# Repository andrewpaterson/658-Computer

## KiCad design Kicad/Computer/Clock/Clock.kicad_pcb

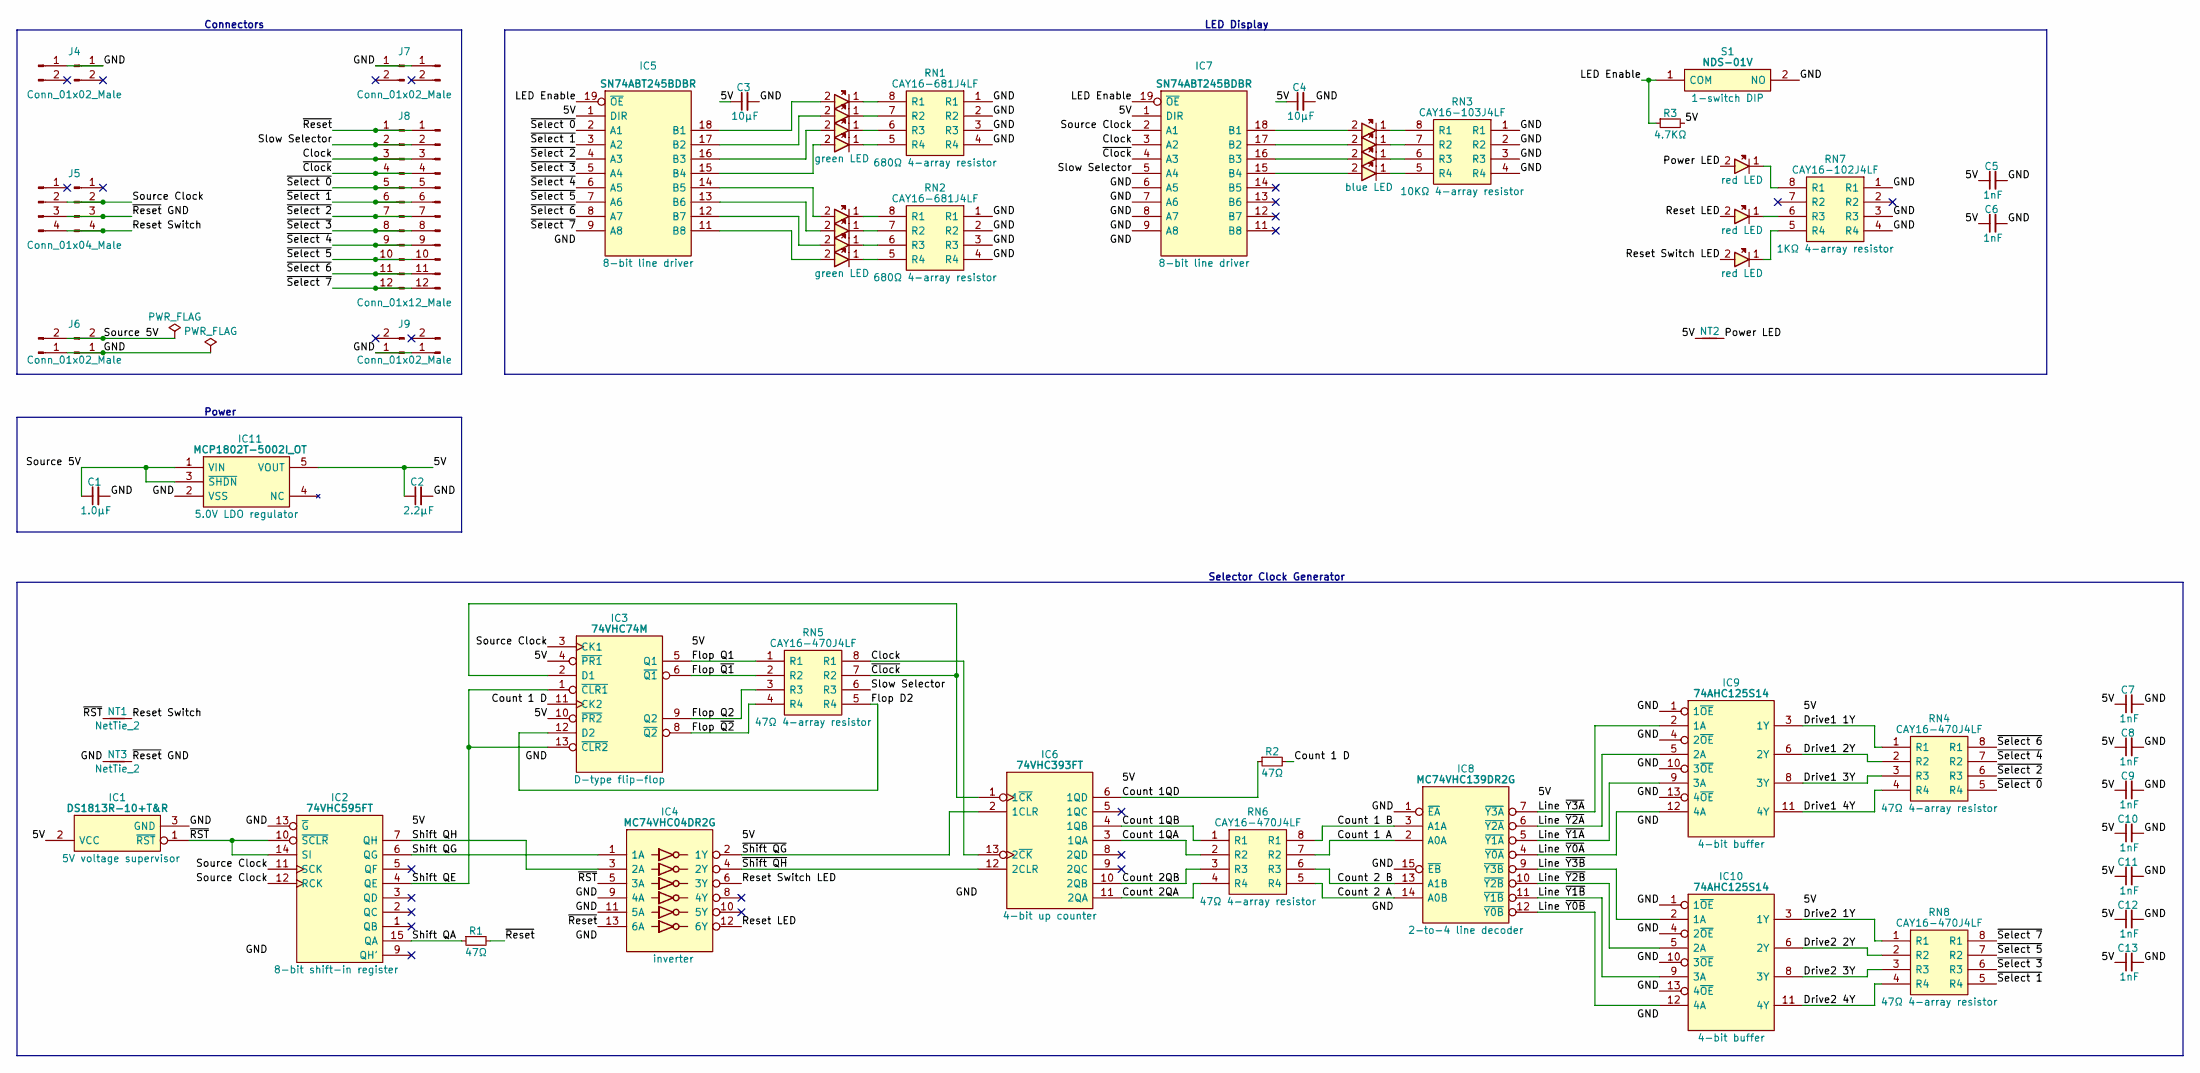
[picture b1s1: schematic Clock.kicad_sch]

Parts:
C1, C2, C3, C4, C5, C6, C7, C8, C9, C10, C11, C12, C13: C_0805
IC1: DS1813R-10+T&R; SOT95P237X112-3N; Mouser Part Number 700-DS1813R-10T&R
IC2: 74VHC595FT; SOP65P640X120-16N; Manufacturer_Part_Number 74VHC595FT; Mouser Part Number 757-74VHC595FT
IC3: 74VHC74M; SOIC127P600X175-14N; Manufacturer_Part_Number 74VHC74M; Mouser Part Number 512-74VHC74M
IC4: MC74VHC04DR2G; SOIC127P600X175-14N; Manufacturer_Part_Number MC74VHC04DR2G; Mouser Part Number 863-MC74VHC04DR2G
IC5, IC7: SN74ABT245BDBR; SOP65P780X200-20N; Manufacturer_Part_Number SN74ABT245BDBR; Mouser Part Number 595-SN74ABT245BDBR
IC6: 74VHC393FT; SOP65P640X120-14N; Manufacturer_Part_Number 74VHC393FT; Mouser Part Number 757-74VHC393FT
IC8: MC74VHC139DR2G; SOIC127P602X173-16N; Manufacturer_Part_Number MC74VHC139DTR2G; Mouser Part Number 863-MC74VHC139DTR2G
IC9, IC10: 74AHC125S14; SOIC127P600X173-14N; Manufacturer_Part_Number 74AHC125S14-13; Mouser Part Number 621-74AHC125S14-13
IC11: MCP1802T-5002I_OT; SOT95P270X145-5N; Manufacturer_Part_Number MCP1802T-5002I/OT; Mouser Part Number 579-MCP1802T-5002IOT
J1, J3, J4, J6, J7, J9, J10, J12: Conn_01x02_Male
J2, J5: Conn_01x04_Male
J8, J11: Conn_01x12_Male
LD10, LD11, LD12: 150224BS73100A; Manufacturer_Part_Number 150224BS73100A; Mouser Part Number 710-150224BS73100A
LD13, LD14, LD15: 150224SS73100; 150224SS73100A; Manufacturer_Part_Number 150224SS73100; Mouser Part Number 710-150224SS73100
LED1, LED2, LED3, LED4, LED5, LED6, LED7, LED8: 150224VS73100A; Manufacturer_Part_Number 150224VS73100A; Mouser Part Number 710-150224VS73100A
LED9: 150224BS73100A; Manufacturer_Part_Number 150224BS73100A; Mouser Part Number 710-150224BS73100A
NT1, NT3: NetTie_2
NT2: NetTie; NetTie-2_SMD_Pad0.5mm
R1, R2, R3: R_0805
RN1, RN2: CAY16-681J4LF; CAY16-J4; Manufacturer_Part_Number CAY16-681J4LF; Mouser Part Number 652-CAY16-681J4LF
RN3: CAY16-103J4LF; CAY16-J4; Manufacturer_Part_Number CAY16-103J4LF; Mouser Part Number 652-CAY16-103J4LF
RN4, RN5, RN6, RN8: CAY16-470J4LF; CAY16470J4LF; Manufacturer_Part_Number CAY16-470J4LF; Mouser Part Number 652-CAY16-470J4LF
RN7: CAY16-102J4LF; CAY16-J4; Manufacturer_Part_Number CAY16-102J4LF; Mouser Part Number 652-CAY16-102J4LF
S1: NDS-01V; NDS01V; Mouser Part Number 113-NDS01V

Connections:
5V: C2.1, C3.1, C4.1, C5.1, C6.1, C7.1, C8.1, C9.1, C10.1, C11.1, C12.1, C13.1, IC1.2 (VCC), IC2.16 (5V), IC3.4 (~PR1), IC3.10 (~PR2), IC3.14 (5V), IC4.14 (5V), IC5.1 (DIR), IC5.20 (5V), IC6.14 (5V), IC7.1 (DIR), IC7.20 (5V), IC8.16 (5V), IC9.14 (VCC), IC10.14 (VCC), IC11.5 (VOUT), NT2.1, R3.2
/Clock: IC6.13 (2~CK), IC7.3 (A2), J8.3, J11.3, RN5.8 (R1)
/Count 1 A: IC8.2 (A0A), RN6.7 (R2)
/Count 1 B: IC8.3 (A1A), RN6.8 (R1)
/Count 1 D: IC3.11 (CK2), R2.2
/Count 1QA: IC6.3 (1QA), RN6.2 (R2)
/Count 1QB: IC6.4 (1QB), RN6.1 (R1)
/Count 1QD: IC6.6 (1QD), R2.1
/Count 2 A: IC8.14 (A0B), RN6.5 (R4)
/Count 2 B: IC8.13 (A1B), RN6.6 (R3)
/Count 2QA: IC6.11 (2QA), RN6.4 (R4)
/Count 2QB: IC6.10 (2QB), RN6.3 (R3)
/Drive1 1Y: IC9.3 (1Y), RN4.1 (R1)
/Drive1 2Y: IC9.6 (2Y), RN4.2 (R2)
/Drive1 3Y: IC9.8 (3Y), RN4.3 (R3)
/Drive1 4Y: IC9.11 (4Y), RN4.4 (R4)
/Drive2 1Y: IC10.3 (1Y), RN8.1 (R1)
/Drive2 2Y: IC10.6 (2Y), RN8.2 (R2)
/Drive2 3Y: IC10.8 (3Y), RN8.3 (R3)
/Drive2 4Y: IC10.11 (4Y), RN8.4 (R4)
/Flop D2: IC3.12 (D2), RN5.5 (R4)
/Flop Q1: IC3.5 (Q1), RN5.1 (R1)
/Flop Q2: IC3.9 (Q2), RN5.3 (R3)
/Flop ~Q1: IC3.6 (~Q1), RN5.2 (R2)
/Flop ~Q2: IC3.8 (~Q2), RN5.4 (R4)
/LED Enable: IC5.19 (~OE), IC7.19 (~OE), R3.1, S1.1 (COM)
/Line ~Y0A: IC8.4 (~Y0A), IC9.12 (4A)
/Line ~Y0B: IC8.12 (~Y0B), IC10.12 (4A)
/Line ~Y1A: IC8.5 (~Y1A), IC9.9 (3A)
/Line ~Y1B: IC8.11 (~Y1B), IC10.9 (3A)
/Line ~Y2A: IC8.6 (~Y2A), IC9.5 (2A)
/Line ~Y2B: IC8.10 (~Y2B), IC10.5 (2A)
/Line ~Y3A: IC8.7 (~Y3A), IC9.2 (1A)
/Line ~Y3B: IC8.9 (~Y3B), IC10.2 (1A)
/Power LED: LD13.2, NT2.2
/Reset LED: IC4.12 (6Y), LD14.2
/Reset Switch: J2.4, J5.4, NT1.1
/Reset Switch LED: IC4.6 (3Y), LD15.2
/Shift QA: IC2.15 (QA), R1.1
/Shift QE: IC2.4 (QE), IC3.1 (~CLR1), IC3.13 (~CLR2)
/Shift QG: IC2.6 (QG), IC4.1 (1A)
/Shift QH: IC2.7 (QH), IC4.3 (2A)
/Slow Selector: IC7.5 (A4), J8.2, J11.2, RN5.6 (R3)
/Source 5V: C1.1, IC11.1 (VIN), IC11.3 (~SHDN), J3.2, J6.2
/Source Clock: IC2.11 (SCK), IC2.12 (RCK), IC3.3 (CK1), IC7.2 (A1), J2.2, J5.2
/~Clock: IC3.2 (D1), IC6.1 (1~CK), IC7.4 (A3), J8.4, J11.4, RN5.7 (R2)
/~RST: IC1.1 (~RST), IC2.10 (~SCLR), IC2.14 (SI), IC4.5 (3A), NT1.2
/~Reset: IC4.13 (6A), J8.1, J11.1, R1.2
/~Reset GND: J2.3, J5.3, NT3.1
/~Select 0: IC5.2 (A1), J8.5, J11.5, RN4.5 (R4)
/~Select 1: IC5.3 (A2), J8.6, J11.6, RN8.5 (R4)
/~Select 2: IC5.4 (A3), J8.7, J11.7, RN4.6 (R3)
/~Select 3: IC5.5 (A4), J8.8, J11.8, RN8.6 (R3)
/~Select 4: IC5.6 (A5), J8.9, J11.9, RN4.7 (R2)
/~Select 5: IC5.7 (A6), J8.10, J11.10, RN8.7 (R2)
/~Select 6: IC5.8 (A7), J8.11, J11.11, RN4.8 (R1)
/~Select 7: IC5.9 (A8), J8.12, J11.12, RN8.8 (R1)
/~Shift QG: IC4.2 (1Y), IC6.2 (1CLR)
/~Shift QH: IC4.4 (2Y), IC6.12 (2CLR)
GND: C1.2, C2.2, C3.2, C4.2, C5.2, C6.2, C7.2, C8.2, C9.2, C10.2, C11.2, C12.2, C13.2, IC1.3 (GND), IC2.8 (GND), IC2.13 (~G), IC3.7 (GND), IC4.7 (GND), IC4.9 (4A), IC4.11 (5A), IC5.10 (GND), IC6.7 (GND), IC7.6 (A5), IC7.7 (A6), IC7.8 (A7), IC7.9 (A8), IC7.10 (GND), IC8.1 (~EA), IC8.8 (GND), IC8.15 (~EB), IC9.1 (1~OE), IC9.4 (2~OE), IC9.7 (GND), IC9.10 (3~OE), IC9.13 (4~OE), IC10.1 (1~OE), IC10.4 (2~OE), IC10.7 (GND), IC10.10 (3~OE), IC10.13 (4~OE), IC11.2 (VSS), J1.1, J3.1, J4.1, J6.1, J7.1, J9.1, J10.1, J12.1, NT3.2, RN1.1 (R1), RN1.2 (R2), RN1.3 (R3), RN1.4 (R4), RN2.1 (R1), RN2.2 (R2), RN2.3 (R3), RN2.4 (R4), RN3.1 (R1), RN3.2 (R2), RN3.3 (R3), RN3.4 (R4), RN7.1 (R1), RN7.3 (R3), RN7.4 (R4), S1.2 (NO)
unnamed: IC5.11 (B8), LED8.2
unnamed: IC5.12 (B7), LED7.2
unnamed: IC5.13 (B6), LED6.2
unnamed: IC5.14 (B5), LED5.2
unnamed: IC5.15 (B4), LED4.2
unnamed: IC5.16 (B3), LED3.2
unnamed: IC5.17 (B2), LED2.2
unnamed: IC5.18 (B1), LED1.2
unnamed: IC7.15 (B4), LD12.2
unnamed: IC7.16 (B3), LD11.2
unnamed: IC7.17 (B2), LD10.2
unnamed: IC7.18 (B1), LED9.2
unnamed: LD10.1, RN3.7 (R2)
unnamed: LD11.1, RN3.6 (R3)
unnamed: LD12.1, RN3.5 (R4)
unnamed: LD13.1, RN7.8 (R1)
unnamed: LD14.1, RN7.6 (R3)
unnamed: LD15.1, RN7.5 (R4)
unnamed: LED1.1, RN1.8 (R1)
unnamed: LED2.1, RN1.7 (R2)
unnamed: LED3.1, RN1.6 (R3)
unnamed: LED4.1, RN1.5 (R4)
unnamed: LED5.1, RN2.8 (R1)
unnamed: LED6.1, RN2.7 (R2)
unnamed: LED7.1, RN2.6 (R3)
unnamed: LED8.1, RN2.5 (R4)
unnamed: LED9.1, RN3.8 (R1)

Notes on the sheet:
LED Display
Connectors
Power
Selector Clock Generator

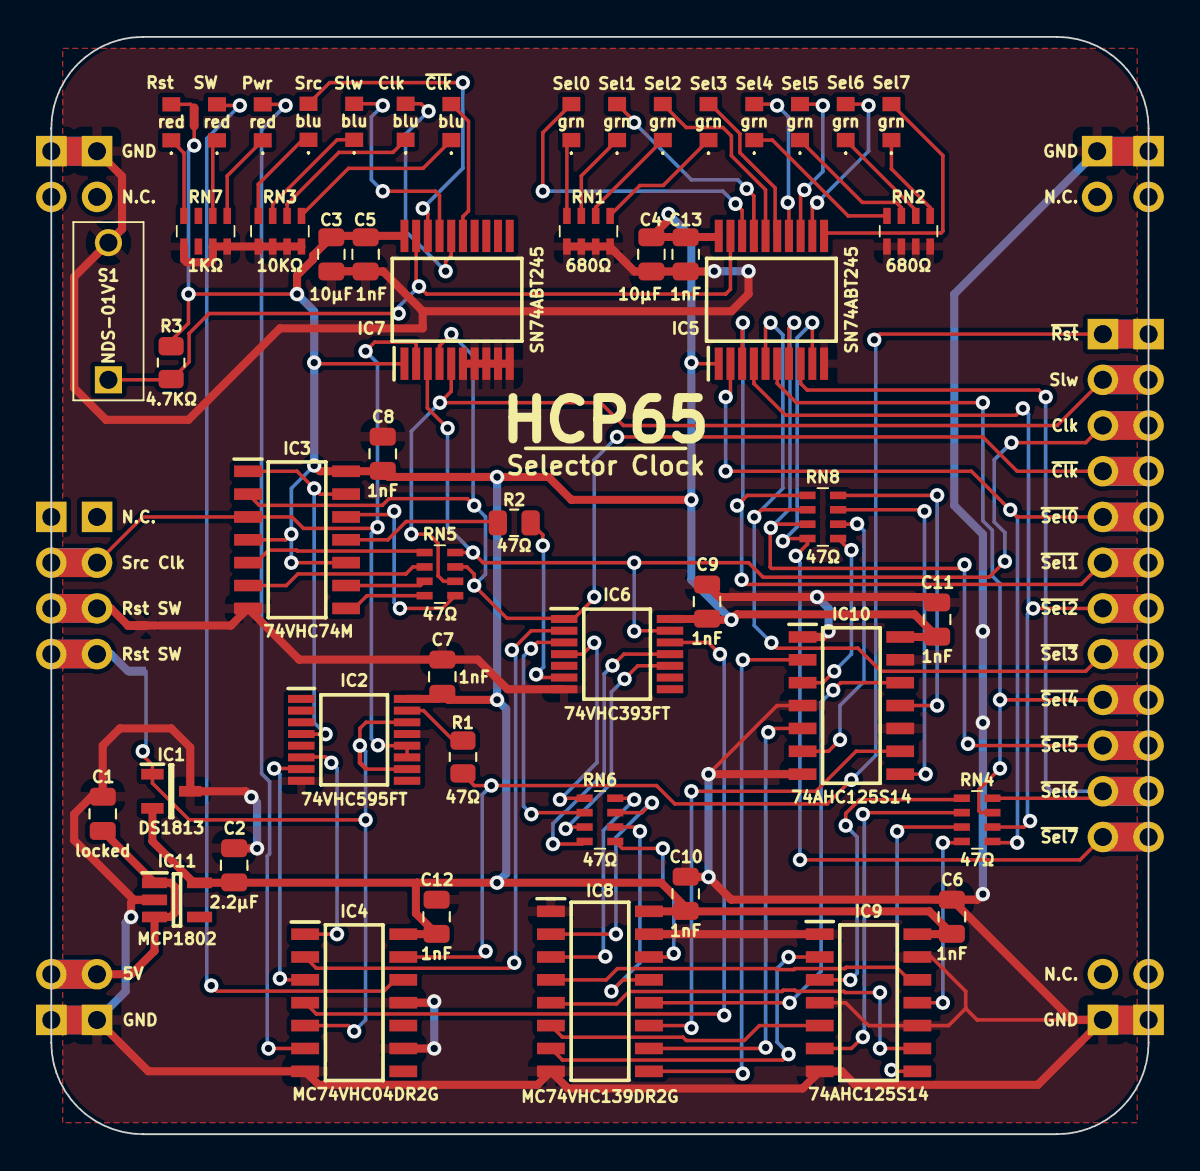
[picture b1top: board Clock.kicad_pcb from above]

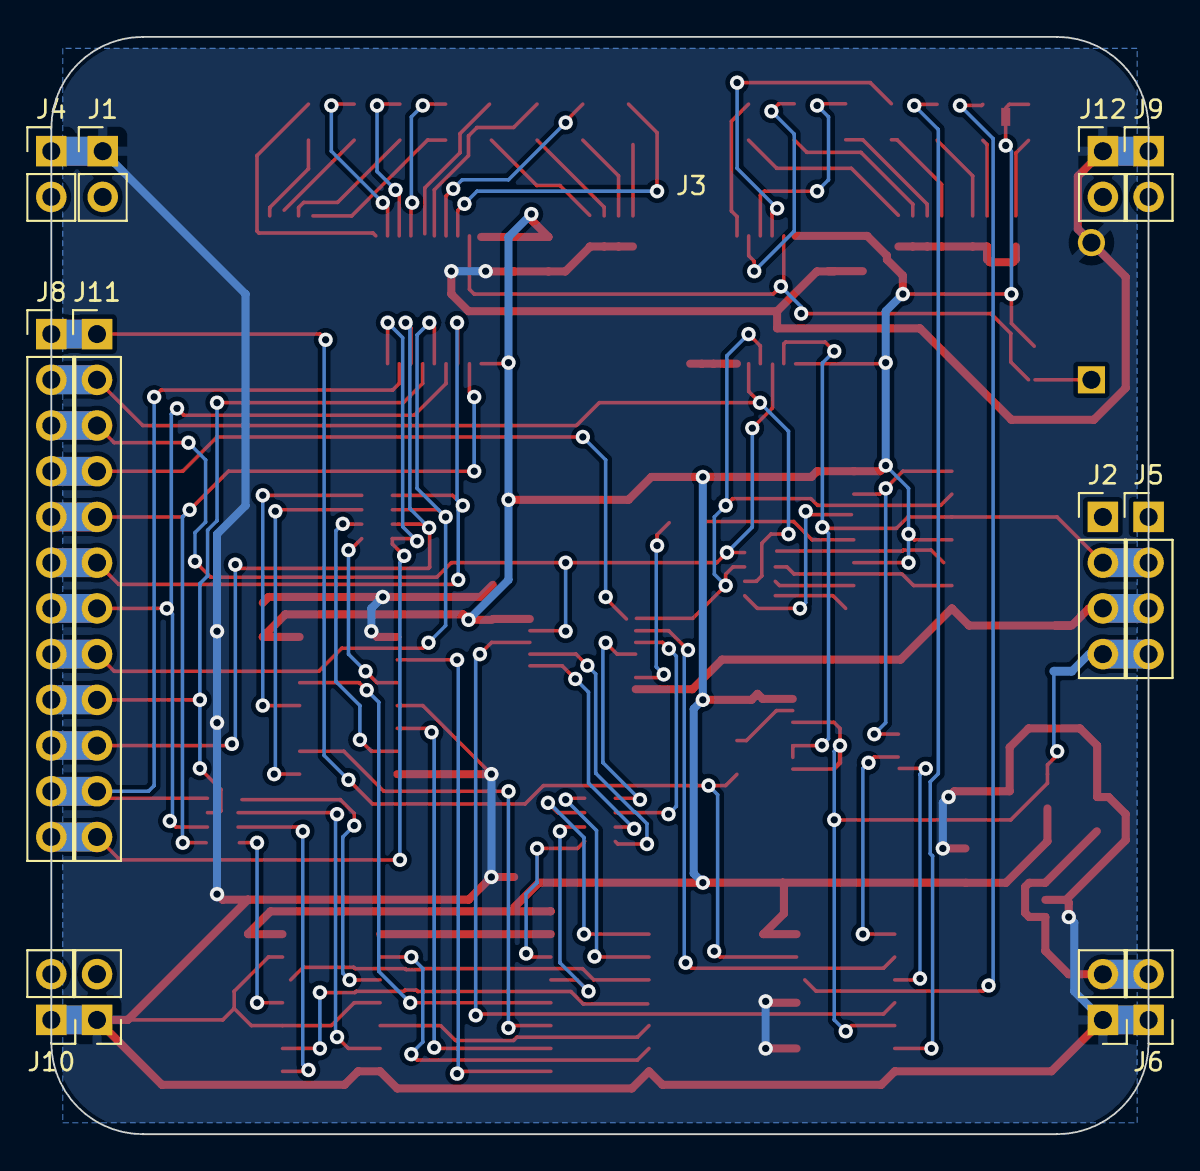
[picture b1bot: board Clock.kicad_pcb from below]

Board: 2 copper layers, 61.0 x 61.0 mm, 66 parts (13 on the bottom side), 87 nets.

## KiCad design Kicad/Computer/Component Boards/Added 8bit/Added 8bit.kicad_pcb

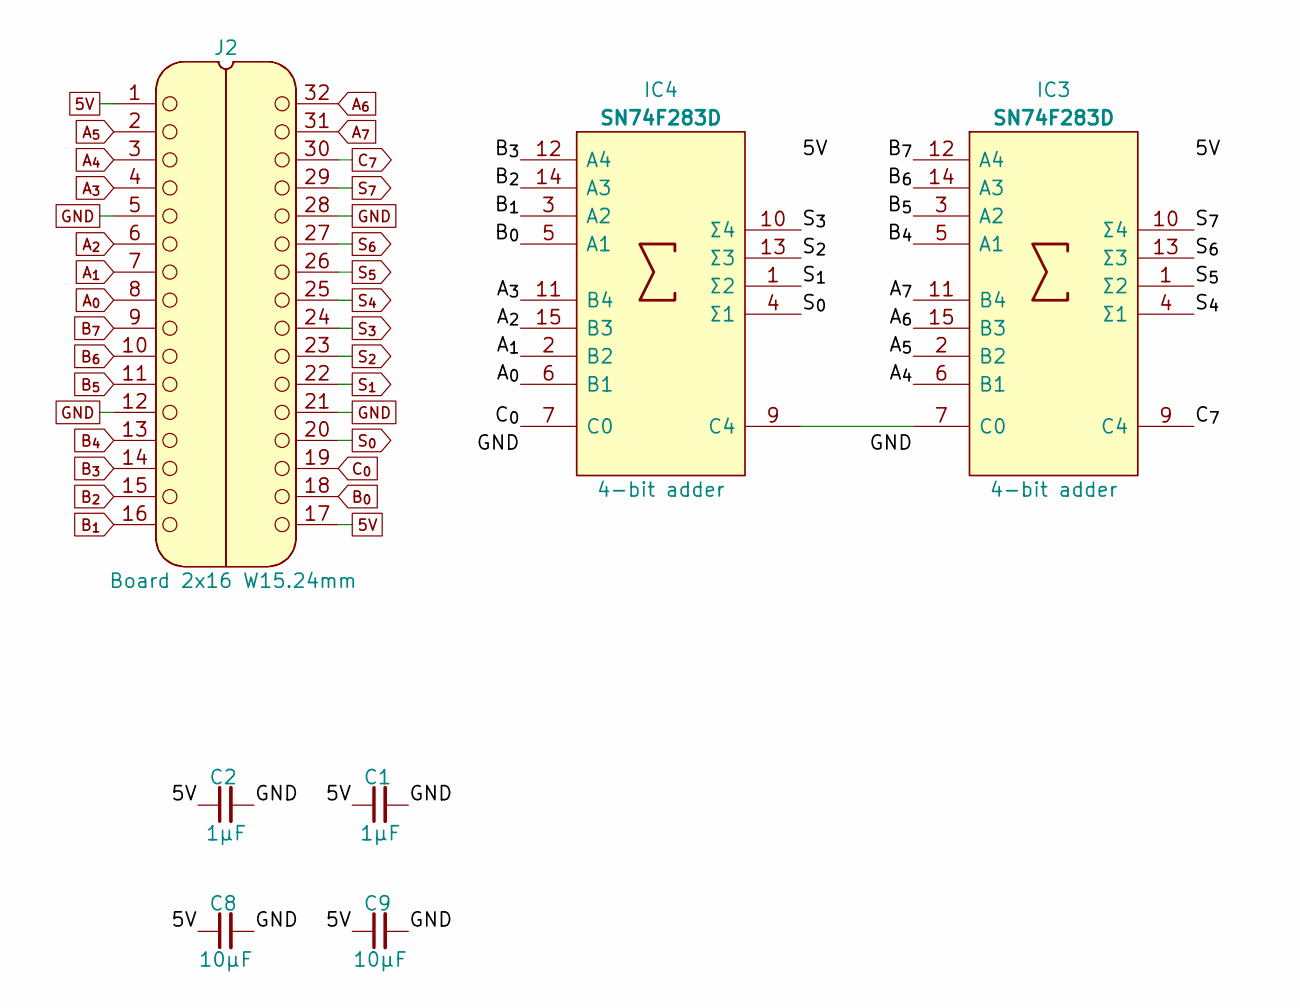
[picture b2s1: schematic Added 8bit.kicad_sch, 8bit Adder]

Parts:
C1, C2: 1μF; C_0805
C8, C9: 10µF; C_0805
IC3, IC4: SN74F283D; SOIC127P600X175-16N; Mouser Part Number 595-SN74F283D
J2: Board 2x16 W15.24mm; DIP-32_Board_W15.24mm

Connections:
5V: C1.1, C2.1, C8.1, C9.1, IC3.16 (5V), IC4.16 (5V), J2.1, J2.17
A_{0}: IC4.6 (B1), J2.8
A_{1}: IC4.2 (B2), J2.7
A_{2}: IC4.15 (B3), J2.6
A_{3}: IC4.11 (B4), J2.4
A_{4}: IC3.6 (B1), J2.3
A_{5}: IC3.2 (B2), J2.2
A_{6}: IC3.15 (B3), J2.32
A_{7}: IC3.11 (B4), J2.31
B_{0}: IC4.5 (A1), J2.18
B_{1}: IC4.3 (A2), J2.16
B_{2}: IC4.14 (A3), J2.15
B_{3}: IC4.12 (A4), J2.14
B_{4}: IC3.5 (A1), J2.13
B_{5}: IC3.3 (A2), J2.11
B_{6}: IC3.14 (A3), J2.10
B_{7}: IC3.12 (A4), J2.9
C_{0}: IC4.7 (C0), J2.19
C_{7}: IC3.9 (C4), J2.30
GND: C1.2, C2.2, C8.2, C9.2, IC3.8 (GND), IC4.8 (GND), J2.5, J2.12, J2.21, J2.28
unnamed: IC3.7 (C0), IC4.9 (C4)
S_{0}: IC4.4 (Σ1), J2.20
S_{1}: IC4.1 (Σ2), J2.22
S_{2}: IC4.13 (Σ3), J2.23
S_{3}: IC4.10 (Σ4), J2.24
S_{4}: IC3.4 (Σ1), J2.25
S_{5}: IC3.1 (Σ2), J2.26
S_{6}: IC3.13 (Σ3), J2.27
S_{7}: IC3.10 (Σ4), J2.29

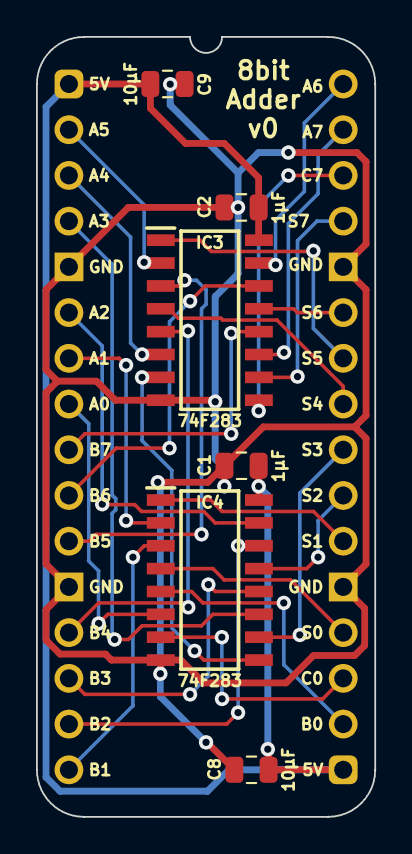
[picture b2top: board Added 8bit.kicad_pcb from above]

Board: 2 copper layers, 18.8 x 43.3 mm, 7 parts (0 on the bottom side), 29 nets.

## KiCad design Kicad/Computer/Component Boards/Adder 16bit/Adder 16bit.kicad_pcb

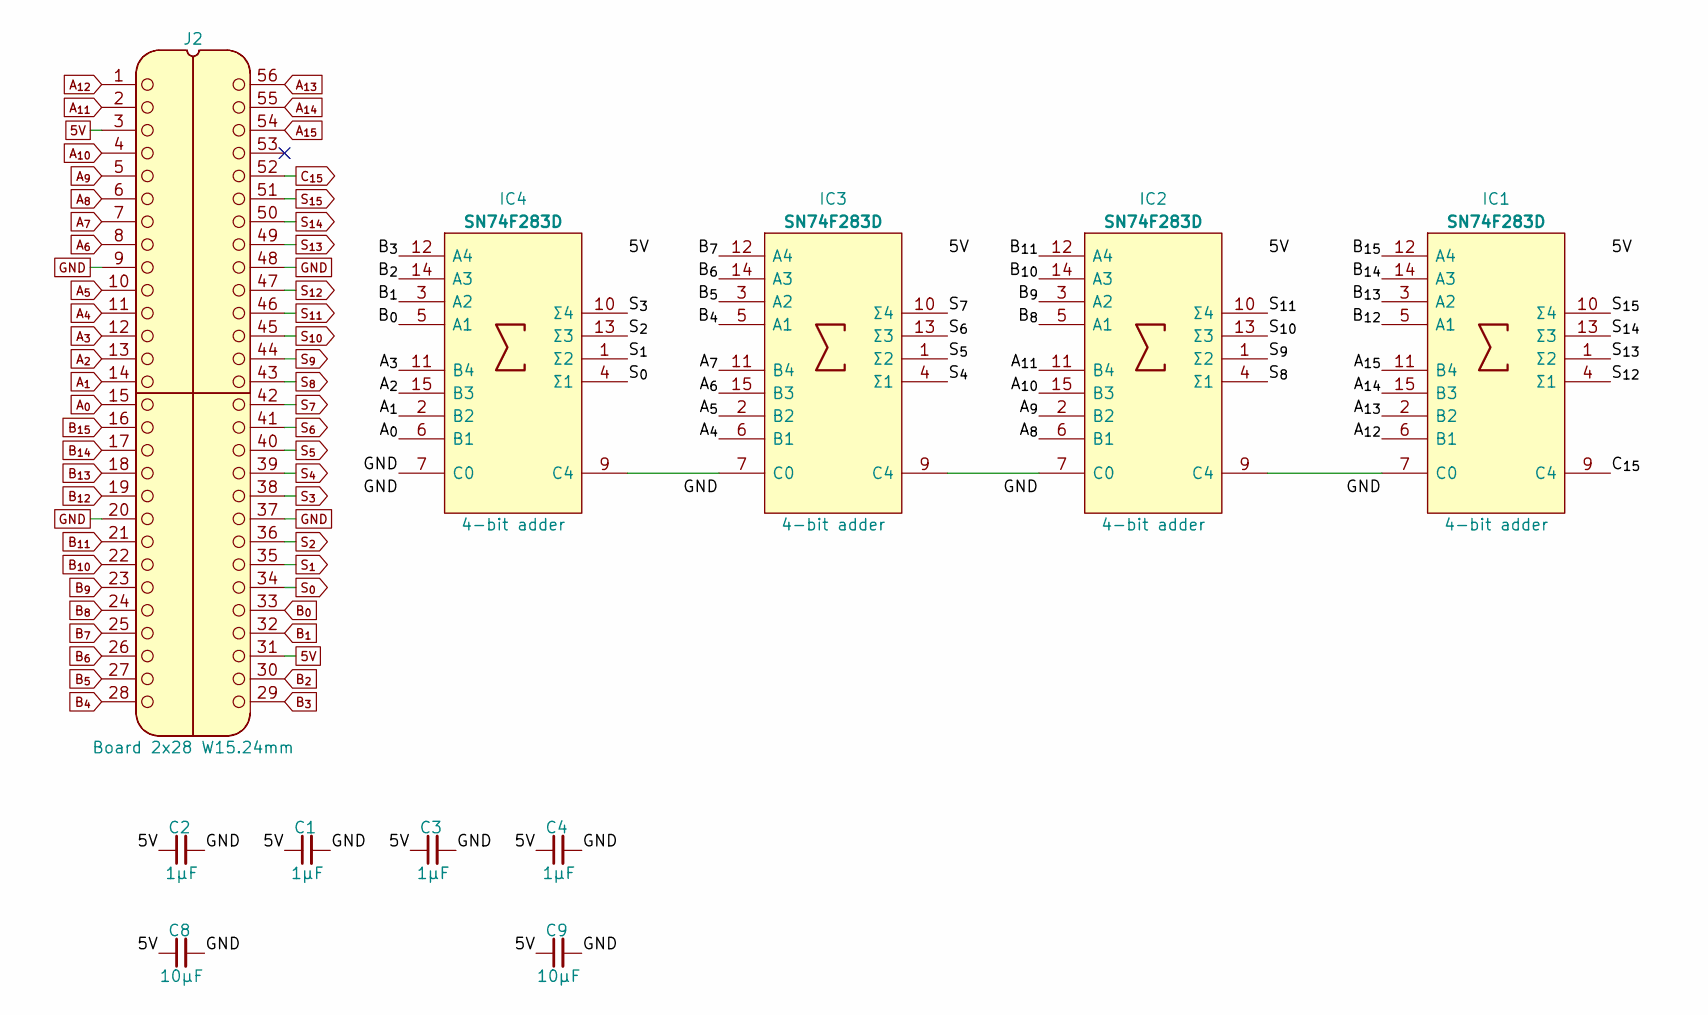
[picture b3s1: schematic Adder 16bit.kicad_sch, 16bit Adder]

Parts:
C1, C2, C3, C4: 1μF; C_0805
C8, C9: 10µF; C_0805
IC1, IC2, IC3, IC4: SN74F283D; SOIC127P600X175-16N; Mouser Part Number 595-SN74F283D
J2: Board 2x28 W15.24mm; DIP-56_Board_W15.24mm

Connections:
5V: C1.1, C2.1, C3.1, C4.1, C8.1, C9.1, IC1.16 (5V), IC2.16 (5V), IC3.16 (5V), IC4.16 (5V), J2.3, J2.31
A_{0}: IC4.6 (B1), J2.15
A_{1}: IC4.2 (B2), J2.14
A_{2}: IC4.15 (B3), J2.13
A_{3}: IC4.11 (B4), J2.12
A_{4}: IC3.6 (B1), J2.11
A_{5}: IC3.2 (B2), J2.10
A_{6}: IC3.15 (B3), J2.8
A_{7}: IC3.11 (B4), J2.7
A_{8}: IC2.6 (B1), J2.6
A_{9}: IC2.2 (B2), J2.5
A_{10}: IC2.15 (B3), J2.4
A_{11}: IC2.11 (B4), J2.2
A_{12}: IC1.6 (B1), J2.1
A_{13}: IC1.2 (B2), J2.56
A_{14}: IC1.15 (B3), J2.55
A_{15}: IC1.11 (B4), J2.54
B_{0}: IC4.5 (A1), J2.33
B_{1}: IC4.3 (A2), J2.32
B_{2}: IC4.14 (A3), J2.30
B_{3}: IC4.12 (A4), J2.29
B_{4}: IC3.5 (A1), J2.28
B_{5}: IC3.3 (A2), J2.27
B_{6}: IC3.14 (A3), J2.26
B_{7}: IC3.12 (A4), J2.25
B_{8}: IC2.5 (A1), J2.24
B_{9}: IC2.3 (A2), J2.23
B_{10}: IC2.14 (A3), J2.22
B_{11}: IC2.12 (A4), J2.21
B_{12}: IC1.5 (A1), J2.19
B_{13}: IC1.3 (A2), J2.18
B_{14}: IC1.14 (A3), J2.17
B_{15}: IC1.12 (A4), J2.16
C_{15}: IC1.9 (C4), J2.52
GND: C1.2, C2.2, C3.2, C4.2, C8.2, C9.2, IC1.8 (GND), IC2.8 (GND), IC3.8 (GND), IC4.7 (C0), IC4.8 (GND), J2.9, J2.20, J2.37, J2.48
unnamed: IC1.7 (C0), IC2.9 (C4)
unnamed: IC2.7 (C0), IC3.9 (C4)
unnamed: IC3.7 (C0), IC4.9 (C4)
S_{0}: IC4.4 (Σ1), J2.34
S_{1}: IC4.1 (Σ2), J2.35
S_{2}: IC4.13 (Σ3), J2.36
S_{3}: IC4.10 (Σ4), J2.38
S_{4}: IC3.4 (Σ1), J2.39
S_{5}: IC3.1 (Σ2), J2.40
S_{6}: IC3.13 (Σ3), J2.41
S_{7}: IC3.10 (Σ4), J2.42
S_{8}: IC2.4 (Σ1), J2.43
S_{9}: IC2.1 (Σ2), J2.44
S_{10}: IC2.13 (Σ3), J2.45
S_{11}: IC2.10 (Σ4), J2.46
S_{12}: IC1.4 (Σ1), J2.47
S_{13}: IC1.1 (Σ2), J2.49
S_{14}: IC1.13 (Σ3), J2.50
S_{15}: IC1.10 (Σ4), J2.51

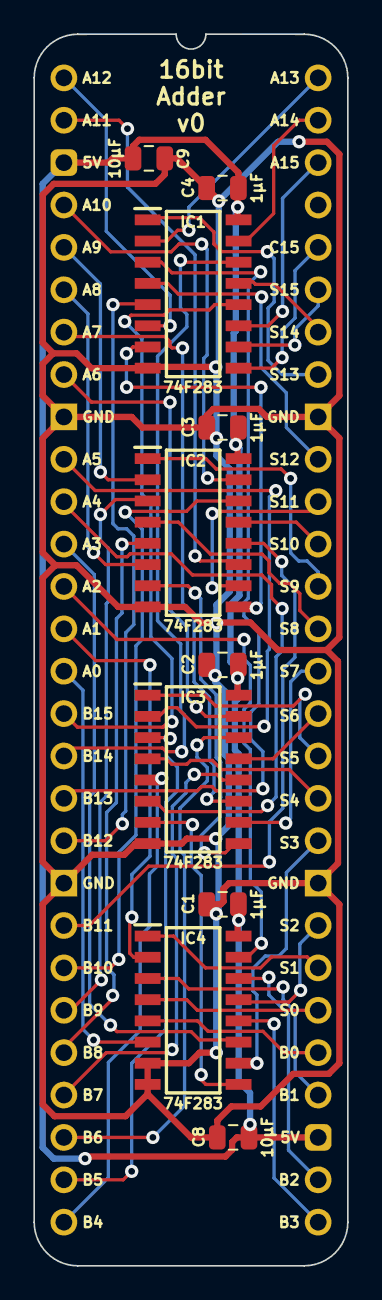
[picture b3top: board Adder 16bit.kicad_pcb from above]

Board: 2 copper layers, 18.8 x 73.8 mm, 11 parts (0 on the bottom side), 54 nets.

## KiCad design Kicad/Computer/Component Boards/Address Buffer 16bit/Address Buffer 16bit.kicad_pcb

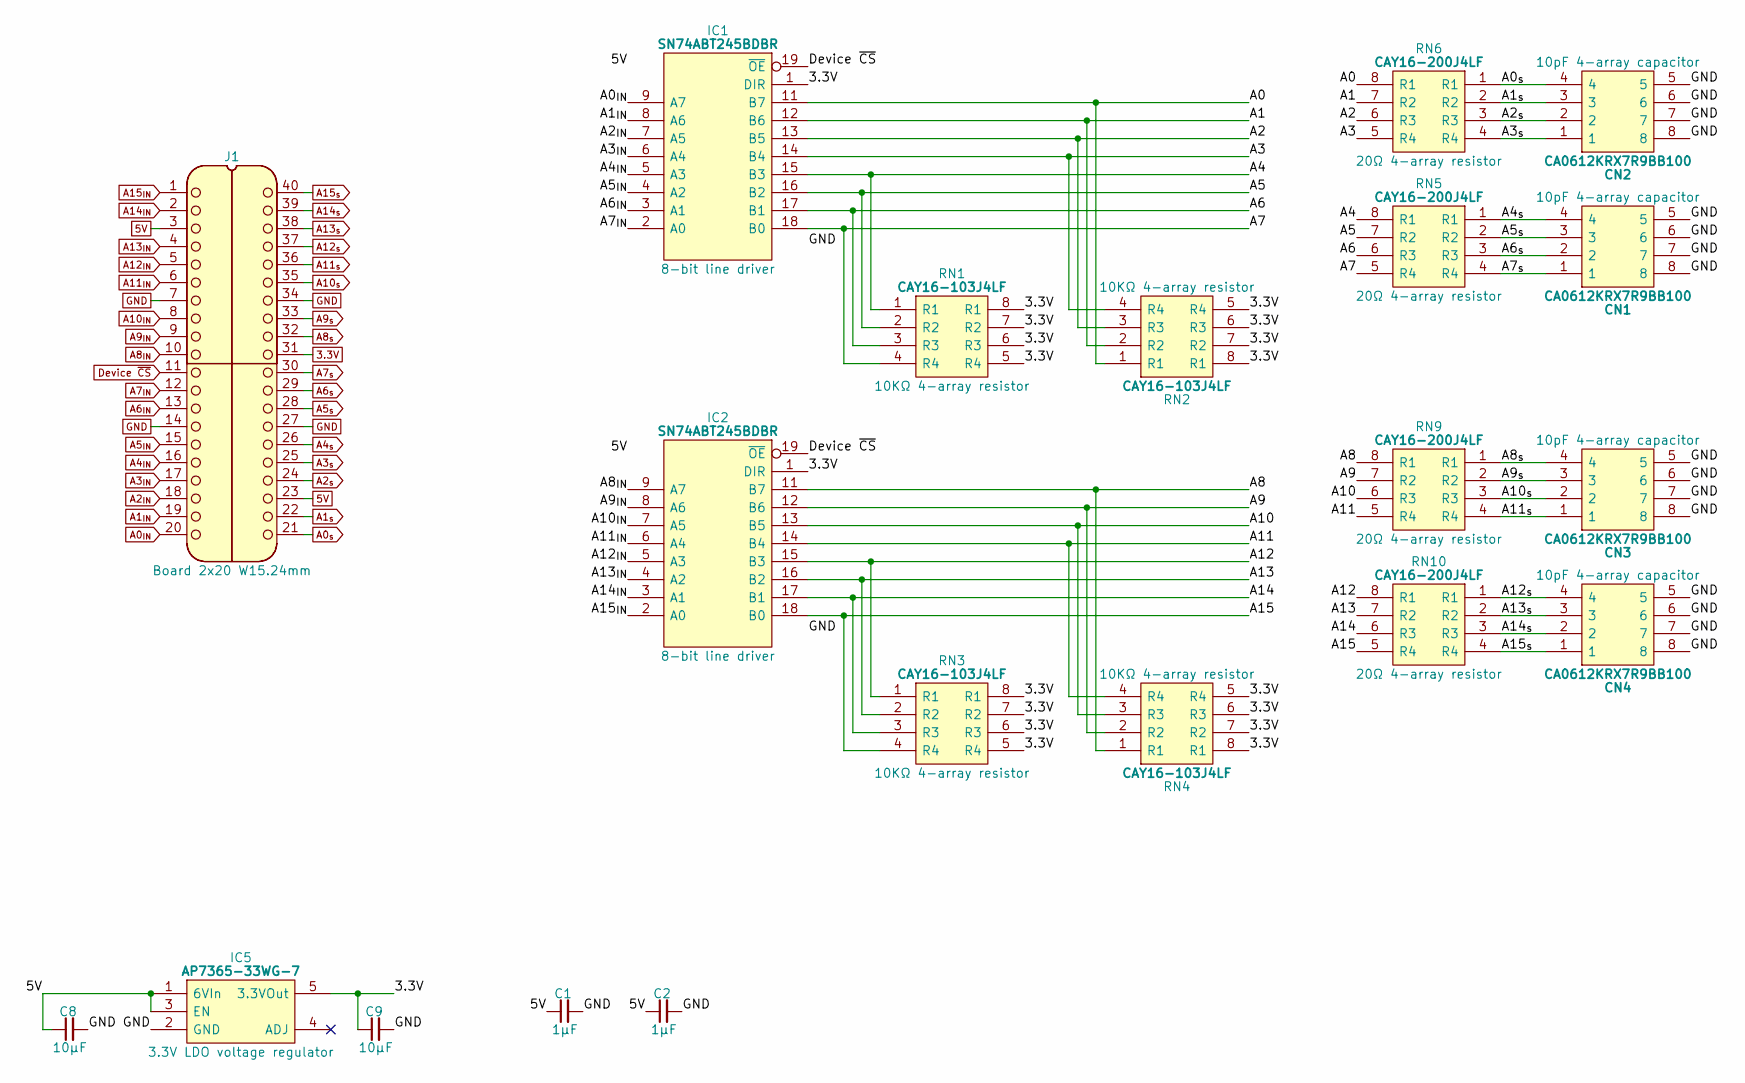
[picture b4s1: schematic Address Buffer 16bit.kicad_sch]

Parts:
C1, C2: 1μF; C_0805
C8, C9: 10µF; C_0805
CN1, CN2, CN3, CN4: CA0612KRX7R9BB100; Manufacturer_Part_Number CA0612KRX7R9BB102; Mouser Part Number 603-CA612KRX7R9BB102
IC1, IC2: SN74ABT245BDBR; SOP65P780X200-20N; Manufacturer_Part_Number SN74ABT245BDBR; Mouser Part Number 595-SN74ABT245BDBR
IC5: AP7365-33WG-7; SOT95P285X130-5N; Manufacturer_Part_Number AP7365-33WG-7; Mouser Part Number 621-AP7365-33WG-7
J1: Board 2x20 W15.24mm; DIP-40_Board_W15.24mm
RN1, RN2, RN3, RN4: CAY16-103J4LF; CAY16-J4; Manufacturer_Part_Number CAY16-103J4LF; Mouser Part Number 652-CAY16-103J4LF
RN5, RN6, RN9, RN10: CAY16-200J4LF; CAY16-F4; Manufacturer_Part_Number CAY16-331J4LF; Mouser Part Number 652-CAY16-331J4LF

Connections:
3.3V: C9.1, IC1.1 (DIR), IC2.1 (DIR), IC5.5 (3.3VOut), J1.31, RN1.5 (R4), RN1.6 (R3), RN1.7 (R2), RN1.8 (R1), RN2.5 (R4), RN2.6 (R3), RN2.7 (R2), RN2.8 (R1), RN3.5 (R4), RN3.6 (R3), RN3.7 (R2), RN3.8 (R1), RN4.5 (R4), RN4.6 (R3), RN4.7 (R2), RN4.8 (R1)
5V: C1.1, C2.1, C8.1, IC1.20 (5V), IC2.20 (5V), IC5.1 (6VIn), IC5.3 (EN), J1.3, J1.23
/A0: IC1.11 (B7), RN2.1 (R1), RN6.8 (R1)
/A1: IC1.12 (B6), RN2.2 (R2), RN6.7 (R2)
/A2: IC1.13 (B5), RN2.3 (R3), RN6.6 (R3)
/A3: IC1.14 (B4), RN2.4 (R4), RN6.5 (R4)
/A4: IC1.15 (B3), RN1.1 (R1), RN5.8 (R1)
/A5: IC1.16 (B2), RN1.2 (R2), RN5.7 (R2)
/A6: IC1.17 (B1), RN1.3 (R3), RN5.6 (R3)
/A7: IC1.18 (B0), RN1.4 (R4), RN5.5 (R4)
/A8: IC2.11 (B7), RN4.1 (R1), RN9.8 (R1)
/A9: IC2.12 (B6), RN4.2 (R2), RN9.7 (R2)
/A10: IC2.13 (B5), RN4.3 (R3), RN9.6 (R3)
/A11: IC2.14 (B4), RN4.4 (R4), RN9.5 (R4)
/A12: IC2.15 (B3), RN3.1 (R1), RN10.8 (R1)
/A13: IC2.16 (B2), RN3.2 (R2), RN10.7 (R2)
/A14: IC2.17 (B1), RN3.3 (R3), RN10.6 (R3)
/A15: IC2.18 (B0), RN3.4 (R4), RN10.5 (R4)
A0_{IN}: IC1.9 (A7), J1.20
A0_{s}: CN2.4, J1.21, RN6.1 (R1)
A1_{IN}: IC1.8 (A6), J1.19
A1_{s}: CN2.3, J1.22, RN6.2 (R2)
A2_{IN}: IC1.7 (A5), J1.18
A2_{s}: CN2.2, J1.24, RN6.3 (R3)
A3_{IN}: IC1.6 (A4), J1.17
A3_{s}: CN2.1, J1.25, RN6.4 (R4)
A4_{IN}: IC1.5 (A3), J1.16
A4_{s}: CN1.4, J1.26, RN5.1 (R1)
A5_{IN}: IC1.4 (A2), J1.15
A5_{s}: CN1.3, J1.28, RN5.2 (R2)
A6_{IN}: IC1.3 (A1), J1.13
A6_{s}: CN1.2, J1.29, RN5.3 (R3)
A7_{IN}: IC1.2 (A0), J1.12
A7_{s}: CN1.1, J1.30, RN5.4 (R4)
A8_{IN}: IC2.9 (A7), J1.10
A8_{s}: CN3.4, J1.32, RN9.1 (R1)
A9_{IN}: IC2.8 (A6), J1.9
A9_{s}: CN3.3, J1.33, RN9.2 (R2)
A10_{IN}: IC2.7 (A5), J1.8
A10_{s}: CN3.2, J1.35, RN9.3 (R3)
A11_{IN}: IC2.6 (A4), J1.6
A11_{s}: CN3.1, J1.36, RN9.4 (R4)
A12_{IN}: IC2.5 (A3), J1.5
A12_{s}: CN4.4, J1.37, RN10.1 (R1)
A13_{IN}: IC2.4 (A2), J1.4
A13_{s}: CN4.3, J1.38, RN10.2 (R2)
A14_{IN}: IC2.3 (A1), J1.2
A14_{s}: CN4.2, J1.39, RN10.3 (R3)
A15_{IN}: IC2.2 (A0), J1.1
A15_{s}: CN4.1, J1.40, RN10.4 (R4)
Device ~CS: IC1.19 (~OE), IC2.19 (~OE), J1.11
GND: C1.2, C2.2, C8.2, C9.2, CN1.5, CN1.6, CN1.7, CN1.8, CN2.5, CN2.6, CN2.7, CN2.8, CN3.5, CN3.6, CN3.7, CN3.8, CN4.5, CN4.6, CN4.7, CN4.8, IC1.10 (GND), IC2.10 (GND), IC5.2 (GND), J1.7, J1.14, J1.27, J1.34

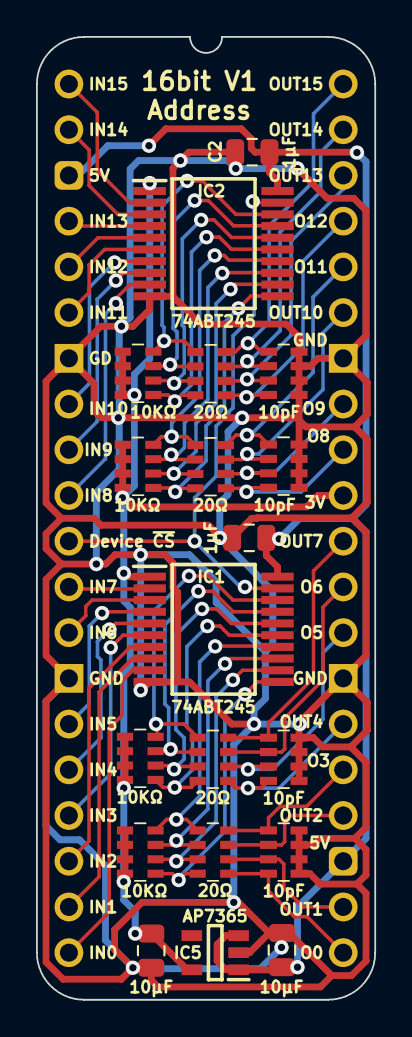
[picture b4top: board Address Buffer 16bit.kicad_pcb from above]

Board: 2 copper layers, 18.8 x 53.5 mm, 20 parts (0 on the bottom side), 52 nets.
